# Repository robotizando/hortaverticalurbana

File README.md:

# Horta Vertical Urbana Livre

Repositório do material desenvolvido para a Horta Vertical Urbana

Veja o artigo completo **[no nosso site Robotizando](https://robotizando.com.br/pt-br/horta-vertical-urbana-livre/)**.

## Roadmap
- Terminar o sistema de agendamento de acionamento das cargas através de uma proto-linguagem

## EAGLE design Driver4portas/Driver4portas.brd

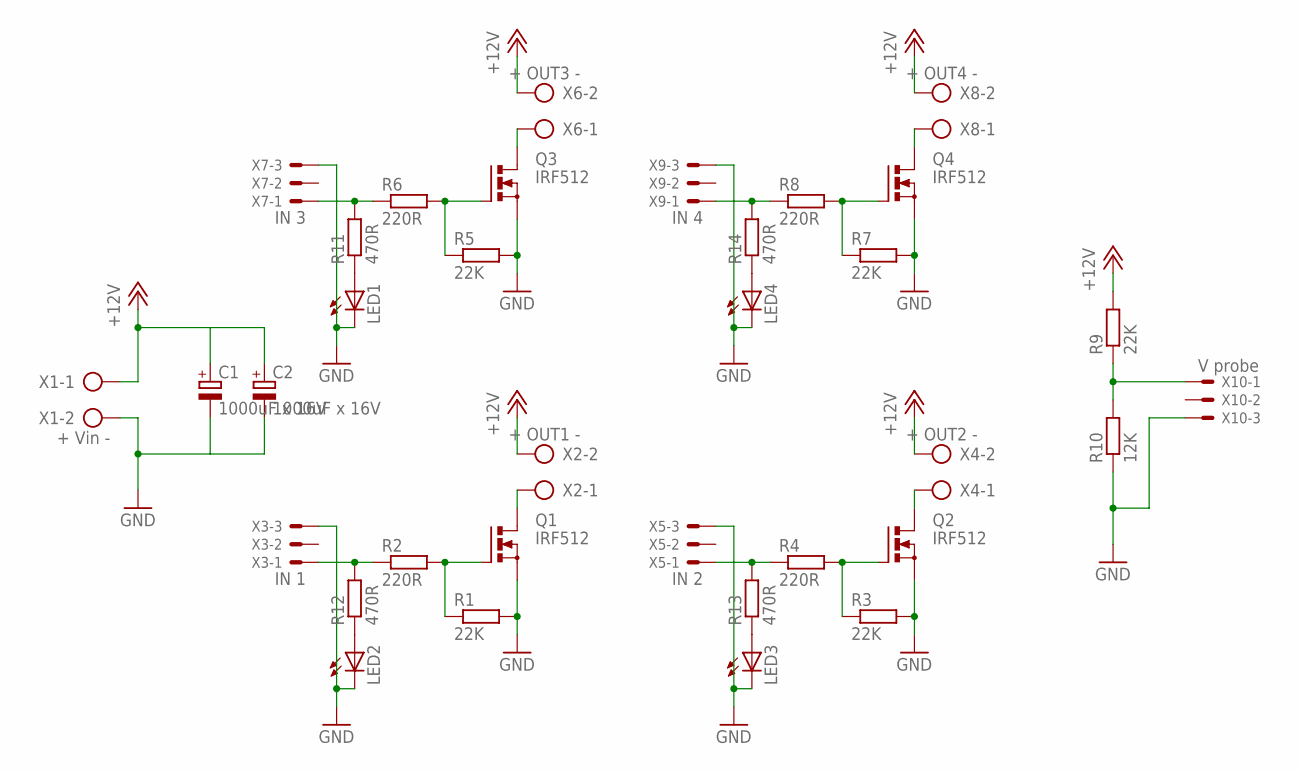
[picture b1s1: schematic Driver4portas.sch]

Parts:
C1, C2: 1000uF x 16V; E2,5-7
LED1, LED2, LED3, LED4: LED3MM
Q1, Q2, Q3, Q4: IRF512; TO220BV
R1, R3, R5, R7, R9: 22K; 0204/7
R2, R4, R6, R8: 220R; 0204/7
R10: 12K; 0204/7
R11, R12, R13, R14: 470R; 0204V
X1: + Vin -; AK500/2
X2: + OUT1 -; AK500/2
X3: IN 1; 22-23-2031
X4: + OUT2 -; AK500/2
X5: IN 2; 22-23-2031
X6: + OUT3 -; AK500/2
X7: IN 3; 22-23-2031
X8: + OUT4 -; AK500/2
X9: IN 4; 22-23-2031
X10: V probe; 22-23-2031

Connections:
+12V: C1.+, C2.+, R9.2, X1.1, X2.2, X4.2, X6.2, X8.2
GND: C1.-, C2.-, LED1.K (C), LED2.K (C), LED3.K (C), LED4.K (C), Q1.S, Q2.S, Q3.S, Q4.S, R1.2, R3.2, R5.2, R7.2, R10.1, X1.2, X3.3, X5.3, X7.3, X9.3, X10.3
unnamed: R2.1, R12.2, X3.1
unnamed: Q1.G, R1.1, R2.2
unnamed: Q1.D, X2.1
unnamed: Q2.G, R3.1, R4.2
unnamed: Q2.D, X4.1
unnamed: R4.1, R13.2, X5.1
unnamed: Q3.G, R5.1, R6.2
unnamed: Q3.D, X6.1
unnamed: R6.1, R11.2, X7.1
unnamed: Q4.G, R7.1, R8.2
unnamed: Q4.D, X8.1
unnamed: R8.1, R14.2, X9.1
unnamed: R9.1, R10.2, X10.1
unnamed: LED1.A, R11.1
unnamed: LED2.A, R12.1
unnamed: LED3.A, R13.1
unnamed: LED4.A, R14.1

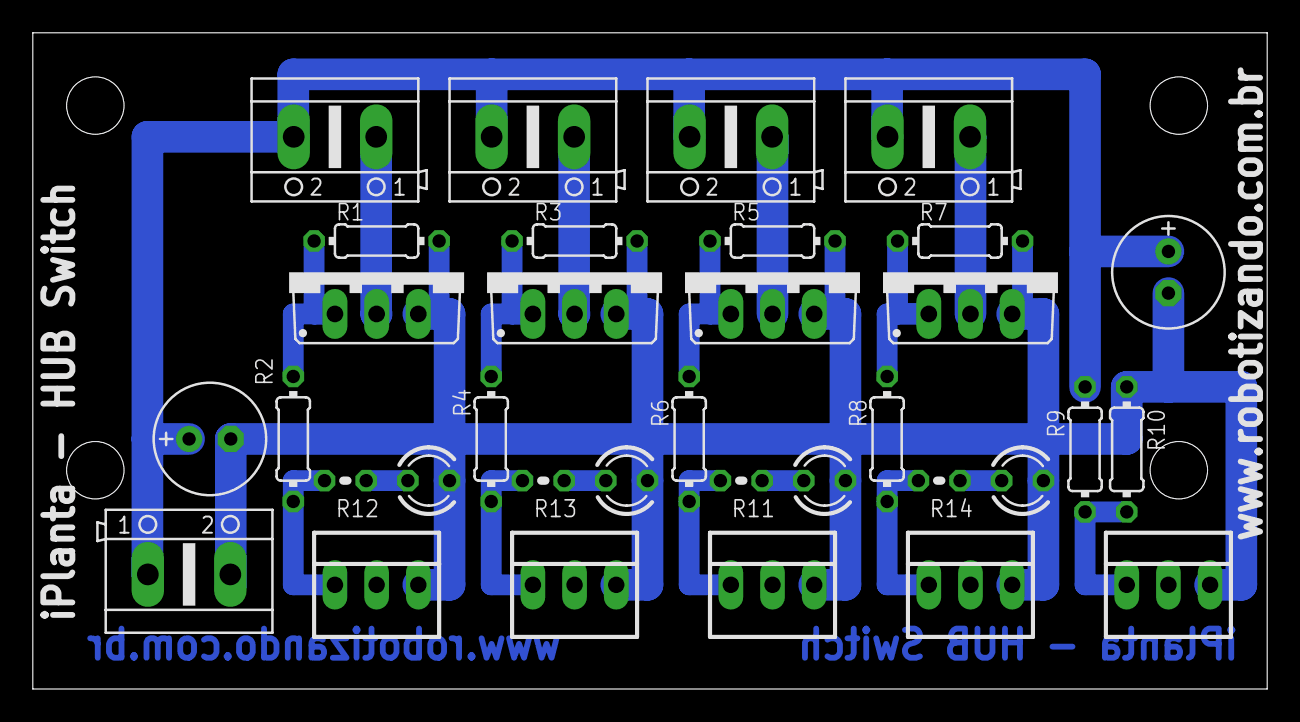
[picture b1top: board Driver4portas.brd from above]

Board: 2 copper layers, 75.2 x 40.0 mm, 34 parts (0 on the bottom side), 19 nets.

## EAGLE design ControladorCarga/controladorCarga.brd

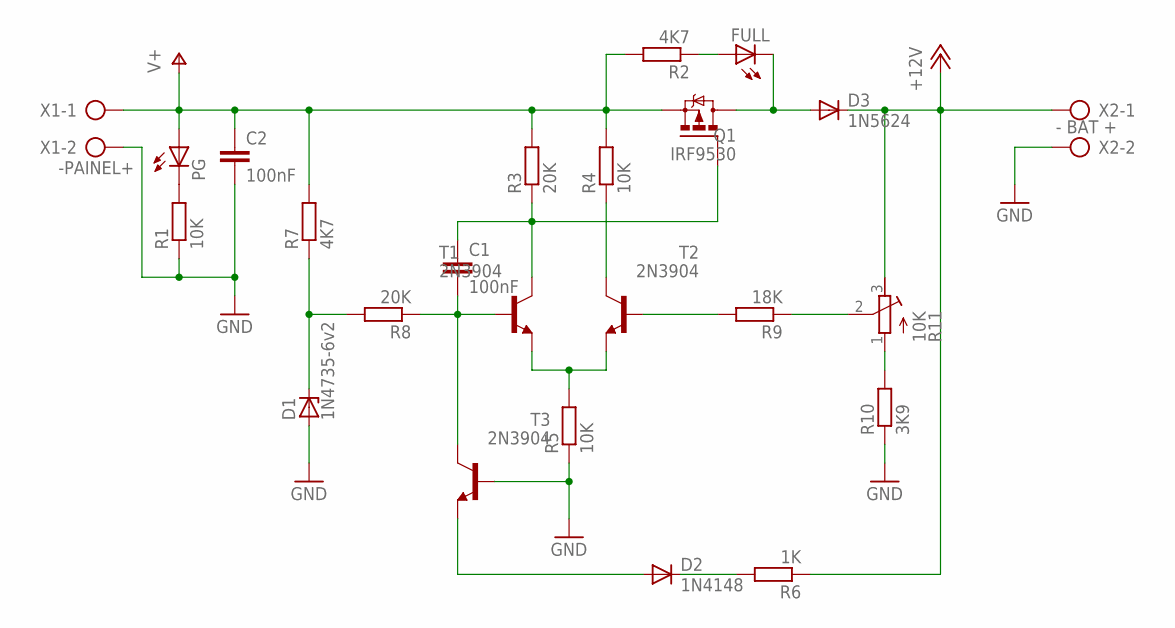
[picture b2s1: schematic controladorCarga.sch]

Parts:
C1, C2: 100nF; C050-025X075
D1: 1N4735-6v2; DO41Z10
D2: 1N4148; DO35-7
D3: 1N5624; DO201-15
FULL: LED5MM
PG: LED5MM
Q1: IRF9530; TO220BV
R1, R4, R5: 10K; 0207/10
R2, R7: 4K7; 0207/10
R3: 20K; 0207/10
R6: 1K; 0207/10
R8: 20K; 0204/7
R9: 18K; 0207/10
R10: 3K9; 0204/7
R11: 10K; RTRIM3339P
T1, T2, T3: 2N3904; TO92
X1: -PAINEL+; AK500/2
X2: - BAT +; AK500/2

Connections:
+12V: D3.C, R6.1, R11.3 (E), X2.1
GND: C2.2, D1.A, R1.1, R5.1, R10.1, T3.2 (B), X1.2, X2.2
unnamed: PG.K (C), R1.2
unnamed: FULL.A, R2.1
unnamed: C1.1, Q1.G, R3.1, T1.1 (C)
unnamed: R4.1, T2.1 (C)
unnamed: D2.C, R6.2
unnamed: R5.2, T1.3 (E), T2.3 (E)
unnamed: D3.A, FULL.K (C), Q1.D
unnamed: D1.C, R7.1, R8.2
unnamed: C1.2, R8.1, T1.2 (B), T3.1 (C)
unnamed: D2.A, T3.3 (E)
unnamed: R9.2, T2.2 (B)
unnamed: R9.1, R11.2 (S)
unnamed: R10.2, R11.1 (A)
V+: C2.1, PG.A, Q1.S, R2.2, R3.2, R4.2, R7.2, X1.1

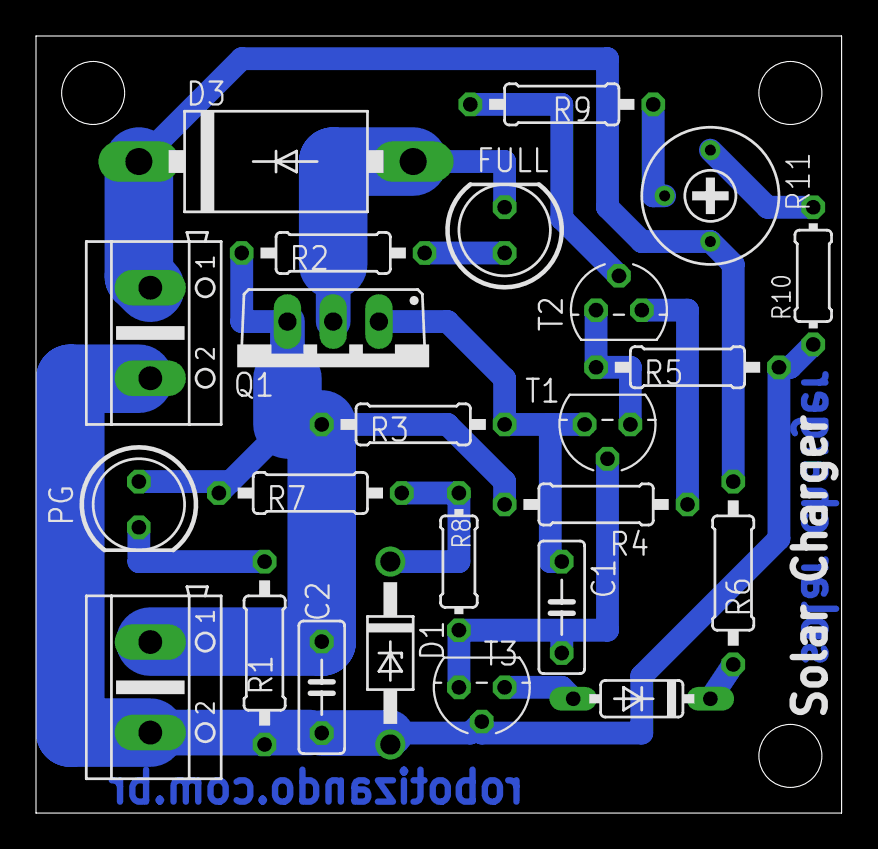
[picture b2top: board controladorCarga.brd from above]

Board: 2 copper layers, 44.8 x 43.2 mm, 24 parts (0 on the bottom side), 16 nets.

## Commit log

2024-05-18 join old and new repositories
